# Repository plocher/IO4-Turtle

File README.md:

# IO4-Turtle
## License: CERN Open Hardware Licence v1.2

IO4 Tortoise driver with occupancy and point position feedback

Carrier board, DFM, feedback LEDS that don't pass tortoise current and
field changable N/R positioning, feedback and frog selection.

This is an adaptation of my older PIC-based ExpressPCB Turtle
project, which is why the version numbers start at 4….  It has
evolved quite a bit, in form factor and functionality as it has
been used on my layout.

This board mounts on a Tortoise via a sweat-soldered right angle
Molex M-M connector, plugs into an [IOB-Turtle](/pages/IOB-Turtle)
or other IO4 compatible port.

The Tortoise provides:

 * OS section occupancy (so you don't throw a turnout out from under a train...),
 * Turnout point position feedback (Normal, in transit, Diverging)
 * easy frog polarity changes for dealing with wiring mishaps
 * easy Normal/Reverse changes for when the Normal route thru a turnout needs to go the other way.
 * Tortoise motor debouncing when it reaches the end of travel
 * feedback LEDs to show Occupancy (yellow) and commanded position (red/green)

It uses my standard IO4 RJ12/6 wiring interface:

 * pin 1: 9-12vDC
 * pin 2: !DIVERGING - Turnout Position Feedback - low = Diverging, high = not diverging
 * pin 3: !NORMAL    - Turnout Position Feedback - low = Normal, high = not normal
 * pin 4: !OCCUPIED  - Detector Feedback - low = occupied, high = empty
 * pin 5: !MOTOR     - Motor Control Input - Low = Normal, High = Diverging
 * pin 6: GND

It also connects to the local DCC track power feed and to the turnout's isolated-for-detection-purposes stock and frog rails.

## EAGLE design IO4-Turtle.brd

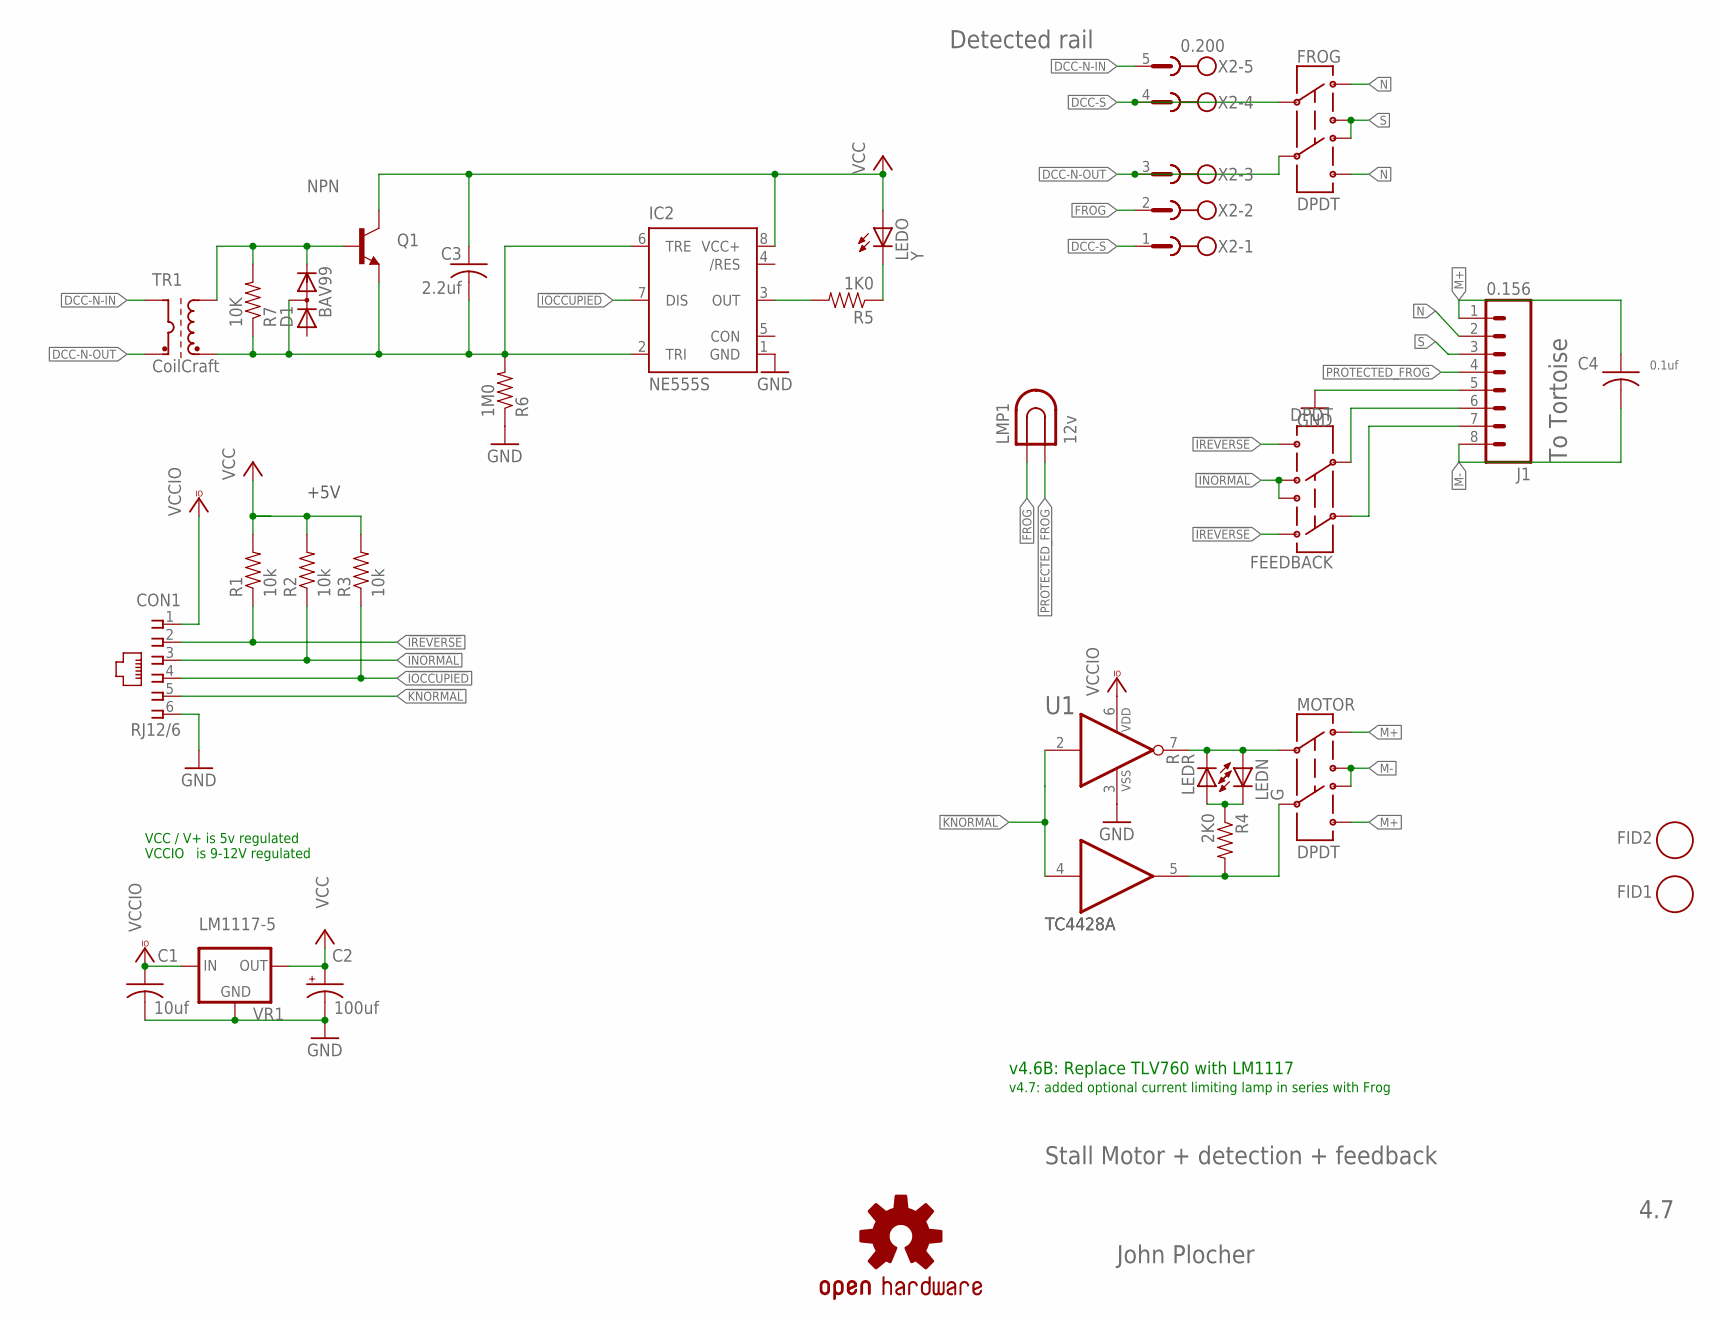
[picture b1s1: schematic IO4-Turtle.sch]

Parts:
C1: 10uf; 0603-CAP
C2: 100uf; PANASONIC_D
C3: 2.2uf; 0603-CAP
C4: 0.1uf; 0805-CAP
CON1: RJ12/6; RJ25-INVERTED
D1: BAV99; SOT23
FEEDBACK: DPDT; 8X8-SQ-PB
FID1, FID2: FIDUCIAL; FIDUCIAL_1MM
FROG: DPDT; 8X8-SQ-PB
IC1: TC4428A; SO-08
IC2: NE555S; SO08
J1: 0.156; KK-156-8-F
LEDN: G; 0603-LED
LEDO: Y; 0603-LED
LEDR: R; 0603-LED
LMP1: 12v; BULB-3156
MOTOR: DPDT; 8X8-SQ-PB
OSHW1: OSHW; OSHW-LOGO-M
Q1: NPN; SOT23
R1, R2, R3: 10k; 0603-RES
R4: 2K0; 0603-RES
R5: 1K0; 0603-RES
R6: 1M0; 0603-RES
R7: 10K; 0603-RES
TR1: CoilCraft; TH-T4
VR1: LM1117-5; SOT223
X2: 0.200; MSTBA5

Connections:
!INORMAL: CON1.3, FEEDBACK.1B, FEEDBACK.2A, R2.1
!IOCCUPIED: CON1.4, IC2.7 (DIS), R3.1
!IREVERSE: CON1.2, FEEDBACK.1A, FEEDBACK.2B, R1.1
!KNORMAL: CON1.5, IC1.2 (I), IC1.4 (I)
+12V: C1.1, CON1.1, IC1.6 (VDD), VR1.3 (IN)
DCC-N-IN: TR1.P1 (DCC-A), X2.5
DCC-N-OUT: FROG.2C, TR1.P2 (DCC-B), X2.3
DCC-S: FROG.1C, X2.1, X2.4
FROG: LMP1.P$1 (1), X2.2
GND: C1.2, C2.-, CON1.6, IC1.3 (VSS), IC2.1 (GND), J1.5, R6.1, VR1.1 (GND)
M+: C4.1, J1.1, MOTOR.1A, MOTOR.2B
M-: C4.2, J1.8, MOTOR.1B, MOTOR.2A
N: FROG.1A, FROG.2B, J1.2
unnamed: IC1.7 (O), LEDN.A, LEDR.C, MOTOR.1C
unnamed: D1.2 (C), Q1.1 (B), R7.2, TR1.S1 (OUT-A)
unnamed: LEDN.C, LEDR.A, R4.1
unnamed: LEDO.C, R5.1
unnamed: IC2.3 (OUT), R5.2
unnamed: FEEDBACK.2C, J1.6
unnamed: FEEDBACK.1C, J1.7
unnamed: IC1.5 (O), MOTOR.2C, R4.2
PROTECTED_FROG: J1.4, LMP1.P$2 (2)
S: FROG.1B, FROG.2A, J1.3
TRIGGER: C3.2, D1.3 (AC), IC2.2 (TRI), IC2.6 (TRE), Q1.2 (E), R6.2, R7.1, TR1.S2 (OUT-B)
V+: C2.+, C3.1, IC2.8 (VCC+), LEDO.A, Q1.3 (C), R1.2, R2.2, R3.2, VR1.2 (OUT), VR1.4 (OUT)

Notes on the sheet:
John Plocher
4.7
Stall Motor + detection + feedback
To Tortoise
Detected rail
v4.6B: Replace TLV760 with LM1117
+5V
v4.7: added optional current limiting lamp in series with Frog
VCC / V+ is 5v regulated VCCIO is 9-12V regulated

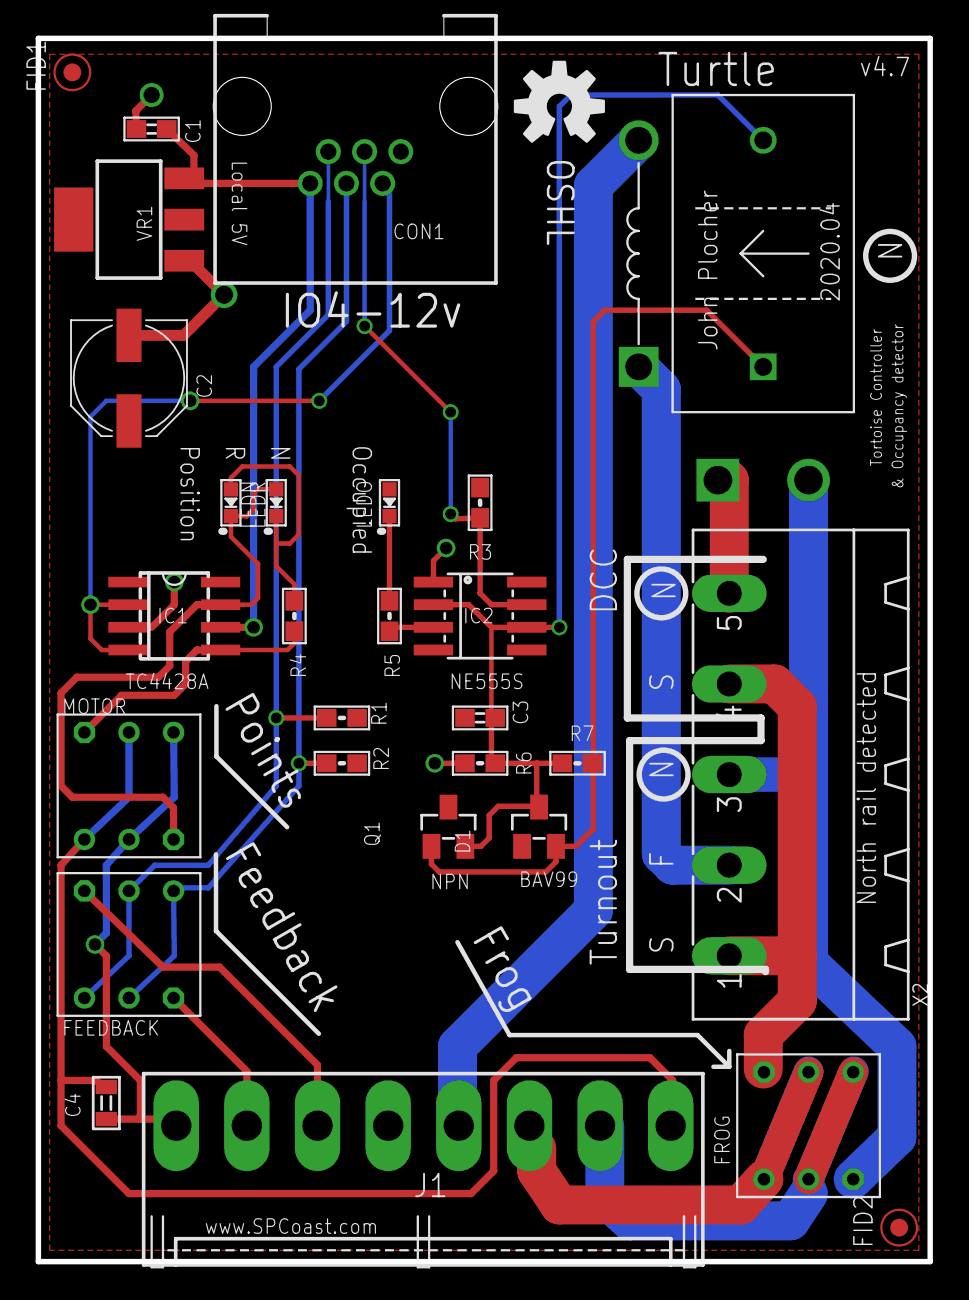
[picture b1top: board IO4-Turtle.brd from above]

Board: 2 copper layers, 50.0 x 68.6 mm, 30 parts (0 on the bottom side), 25 nets.

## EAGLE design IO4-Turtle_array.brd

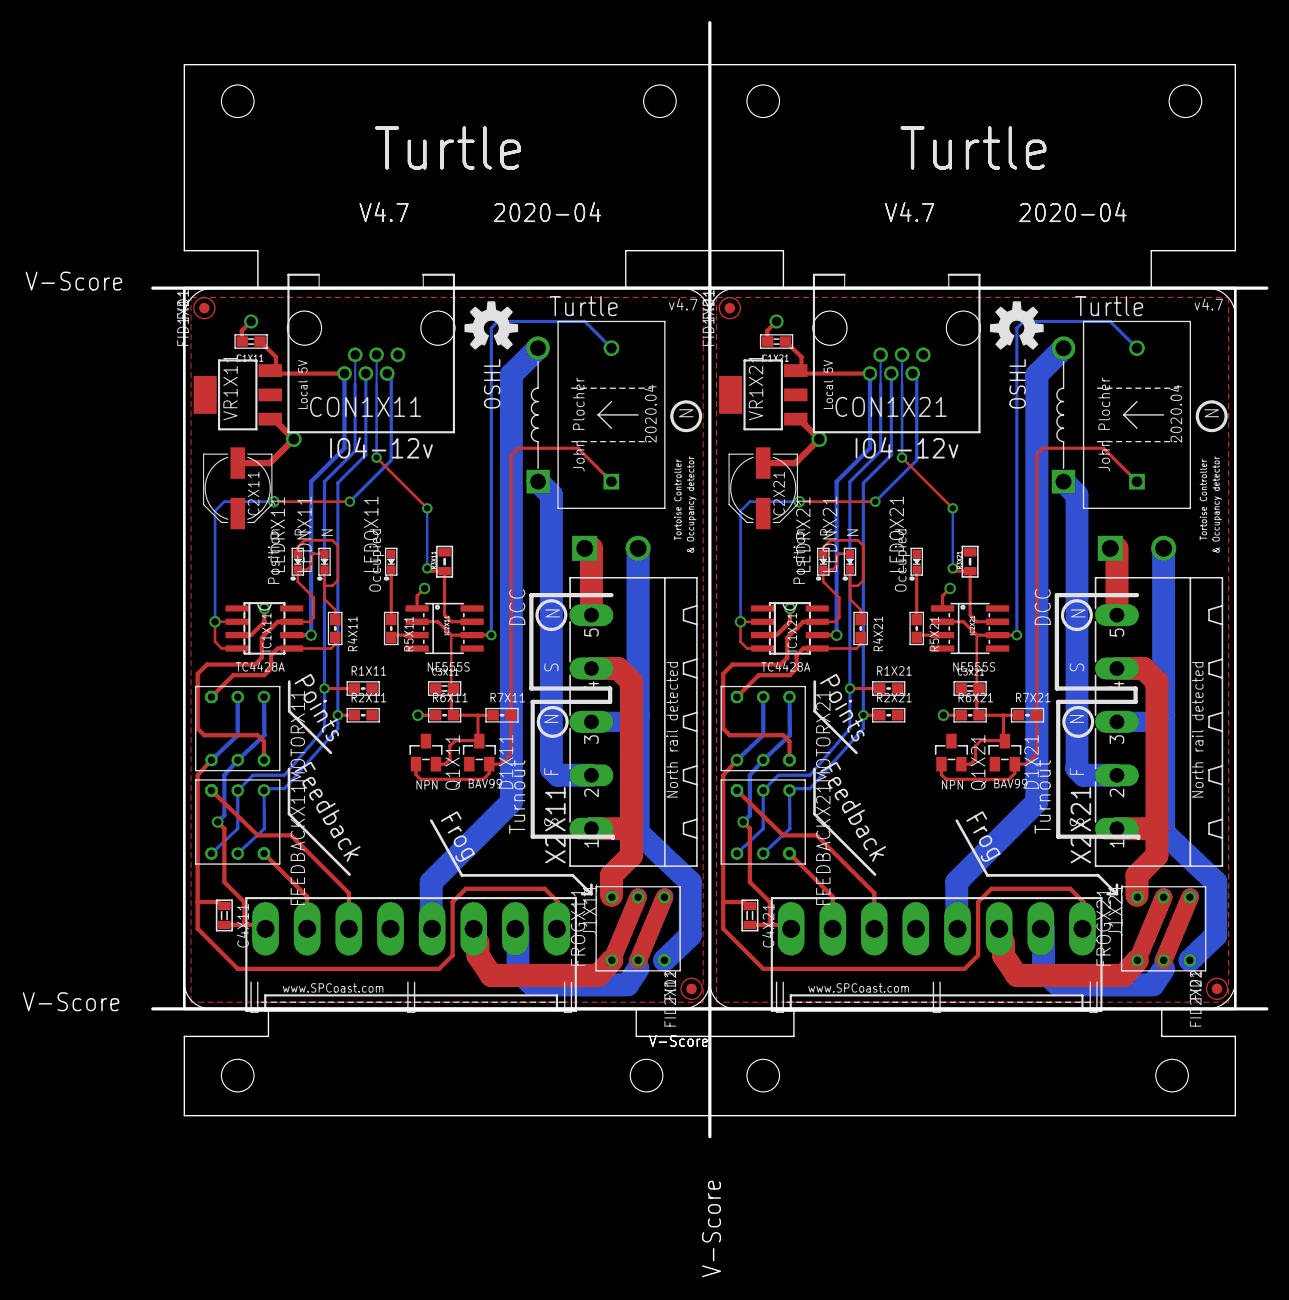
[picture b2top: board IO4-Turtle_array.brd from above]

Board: 2 copper layers, 106.0 x 106.0 mm, 61 parts (0 on the bottom side), 50 nets.

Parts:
C1X11, C1X21: 10uf; 0603-CAP
C2X11, C2X21: 100uf; PANASONIC_D
C3X11, C3X21: 2.2uf; 0603-CAP
C4X11, C4X21: 0.1uf; 0805-CAP
CON1X11, CON1X21: RJ12/6; RJ25-INVERTED
D1X11, D1X21: BAV99; SOT23
FEEDBACKX11, FEEDBACKX21: DPDT; 8X8-SQ-PB
FID1X11, FID1X21, FID2X11, FID2X21: FIDUCIAL; FIDUCIAL_1MM
FROGX11, FROGX21: DPDT; 8X8-SQ-PB
IC1X11, IC1X21: TC4428A; SO-08
IC2X11, IC2X21: NE555S; SO08
J1X11, J1X21: 0.156; KK-156-8-F
LEDNX11, LEDNX21: G; 0603-LED
LEDOX11, LEDOX21: Y; 0603-LED
LEDRX11, LEDRX21: R; 0603-LED
LMP1X11, LMP1X21: 12v; BULB-3156
MOTORX11, MOTORX21: DPDT; 8X8-SQ-PB
OSHW1X11, OSHW1X21: OSHW; OSHW-LOGO-M
Q1X11, Q1X21: NPN; SOT23
R1X11, R1X21, R2X11, R2X21: 10k; 0603-RES
R3X11, R3X21: 10k; 0805-RES
R4X11, R4X21: 2K0; 0603-RES
R5X11, R5X21: 1K0; 0603-RES
R6X11, R6X21: 1M0; 0603-RES
R7X11, R7X21: 10K; 0603-RES
TR1X11, TR1X21: CoilCraft; TH-T4
VR1X11, VR1X21: LM1117-5; SOT223
X2X1: 10x10; BOARD-DINRAIL-2.7IN-5CM-DUAL
X2X11, X2X21: 0.200; MSTBA5

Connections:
!INORMALX11: CON1X11.3, FEEDBACKX11.1B, FEEDBACKX11.2A, R2X11.1
!INORMALX21: CON1X21.3, FEEDBACKX21.1B, FEEDBACKX21.2A, R2X21.1
!IOCCUPIEDX11: CON1X11.4, IC2X11.7, R3X11.1
!IOCCUPIEDX21: CON1X21.4, IC2X21.7, R3X21.1
!IREVERSEX11: CON1X11.2, FEEDBACKX11.1A, FEEDBACKX11.2B, R1X11.1
!IREVERSEX21: CON1X21.2, FEEDBACKX21.1A, FEEDBACKX21.2B, R1X21.1
!KNORMALX11: CON1X11.5, IC1X11.2, IC1X11.4
!KNORMALX21: CON1X21.5, IC1X21.2, IC1X21.4
+12VX11: C1X11.1, CON1X11.1, IC1X11.6, VR1X11.3
+12VX21: C1X21.1, CON1X21.1, IC1X21.6, VR1X21.3
DCC-N-INX11: TR1X11.P1, X2X11.5
DCC-N-INX21: TR1X21.P1, X2X21.5
DCC-N-OUTX11: FROGX11.2C, TR1X11.P2, X2X11.3
DCC-N-OUTX21: FROGX21.2C, TR1X21.P2, X2X21.3
DCC-SX11: FROGX11.1C, X2X11.1, X2X11.4
DCC-SX21: FROGX21.1C, X2X21.1, X2X21.4
FROGX11: LMP1X11.P$1, X2X11.2
FROGX21: LMP1X21.P$1, X2X21.2
GNDX11: C1X11.2, C2X11.-, CON1X11.6, IC1X11.3, IC2X11.1, J1X11.5, R6X11.1, VR1X11.1
GNDX21: C1X21.2, C2X21.-, CON1X21.6, IC1X21.3, IC2X21.1, J1X21.5, R6X21.1, VR1X21.1
M+X11: C4X11.1, J1X11.1, MOTORX11.1A, MOTORX11.2B
M+X21: C4X21.1, J1X21.1, MOTORX21.1A, MOTORX21.2B
M-X11: C4X11.2, J1X11.8, MOTORX11.1B, MOTORX11.2A
M-X21: C4X21.2, J1X21.8, MOTORX21.1B, MOTORX21.2A
unnamed: IC1X11.7, LEDNX11.A, LEDRX11.C, MOTORX11.1C
unnamed: IC1X21.7, LEDNX21.A, LEDRX21.C, MOTORX21.1C
unnamed: D1X11.2, Q1X11.1, R7X11.2, TR1X11.S1
unnamed: D1X21.2, Q1X21.1, R7X21.2, TR1X21.S1
unnamed: LEDNX11.C, LEDRX11.A, R4X11.1
unnamed: LEDNX21.C, LEDRX21.A, R4X21.1
unnamed: LEDOX11.C, R5X11.1
unnamed: LEDOX21.C, R5X21.1
unnamed: IC2X11.3, R5X11.2
unnamed: IC2X21.3, R5X21.2
unnamed: FEEDBACKX11.2C, J1X11.6
unnamed: FEEDBACKX21.2C, J1X21.6
unnamed: FEEDBACKX11.1C, J1X11.7
unnamed: FEEDBACKX21.1C, J1X21.7
unnamed: IC1X11.5, MOTORX11.2C, R4X11.2
unnamed: IC1X21.5, MOTORX21.2C, R4X21.2
NX11: FROGX11.1A, FROGX11.2B, J1X11.2
NX21: FROGX21.1A, FROGX21.2B, J1X21.2
PROTECTED_FROGX11: J1X11.4, LMP1X11.P$2
PROTECTED_FROGX21: J1X21.4, LMP1X21.P$2
SX11: FROGX11.1B, FROGX11.2A, J1X11.3
SX21: FROGX21.1B, FROGX21.2A, J1X21.3
TRIGGERX11: C3X11.2, D1X11.3, IC2X11.2, IC2X11.6, Q1X11.2, R6X11.2, R7X11.1, TR1X11.S2
TRIGGERX21: C3X21.2, D1X21.3, IC2X21.2, IC2X21.6, Q1X21.2, R6X21.2, R7X21.1, TR1X21.S2
V+X11: C2X11.+, C3X11.1, IC2X11.8, LEDOX11.A, Q1X11.3, R1X11.2, R2X11.2, R3X11.2, VR1X11.2, VR1X11.4
V+X21: C2X21.+, C3X21.1, IC2X21.8, LEDOX21.A, Q1X21.3, R1X21.2, R2X21.2, R3X21.2, VR1X21.2, VR1X21.4

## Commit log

2019-11-25 4.6B
2019-12-07 added graphic
2020-04-26 cleanup, replaced LM1117 output cap
2020-04-26 silkscreen cleanup, better power routing
2020-05-04 updated tags
2020-05-30 fixed panelization bug - re-added part values
2020-10-05 added values for connectors
2020-10-06 normalized values

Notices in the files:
parts and their libraries:
SPCoast: http://freedomdefined.org/OSHW Creative Commons - Attribution - ShareAlike 3.0
